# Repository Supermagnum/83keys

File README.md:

# 83keys
A 83 key keyboard, Norwegian QWERTY/DVORAK ISO style.
It's of course possible to use other languages, as the MX cherry switches will accept keycaps with whatever language you need.

It uses 83 1N4148 diodes and three LED's for caps lock,scroll lock, and QWERTY/DVORAK.
It also needs pin headers that accepts the pins from a Teensy++2.0.

That makes it easy to replace the Teensy in the case that something goes wrong.
Since the Teensy++2.0 is mounted in a socket, there is no special training required because there are no need to solder any SMD components. 
I think that that makes it easier to mass produce because little training and special tools are required.

The keyboard layout is located here:
http://www.keyboard-layout-editor.com/#/gists/53284f72c23040b29def237b7399e567

Made using Kicad, that can be found here:
https://kicad-pcb.org/

All footprints for the components needed for the keyboard is included in this GitHub.
That excludes the Teensy++2.0 board and the components needed for it.

Kicad footprints for Teensy 
https://github.com/XenGi/teensy.pretty

Kicad schematic symbols of Teensy modules:
https://github.com/XenGi/teensy_library

QMK is here:
https://qmk.fm/

The handwire folder contains files necessary to make the bottom,top and switch plates for those who want to handwire the keyboard without using a PCB.
It should be compatible with Cherry Stabilizers. 

I hope that the Teensy socket is wired up correctly.
If not,please fork this repository and make the required changes.

Note: The diodes on the schematic diagram is wrong.

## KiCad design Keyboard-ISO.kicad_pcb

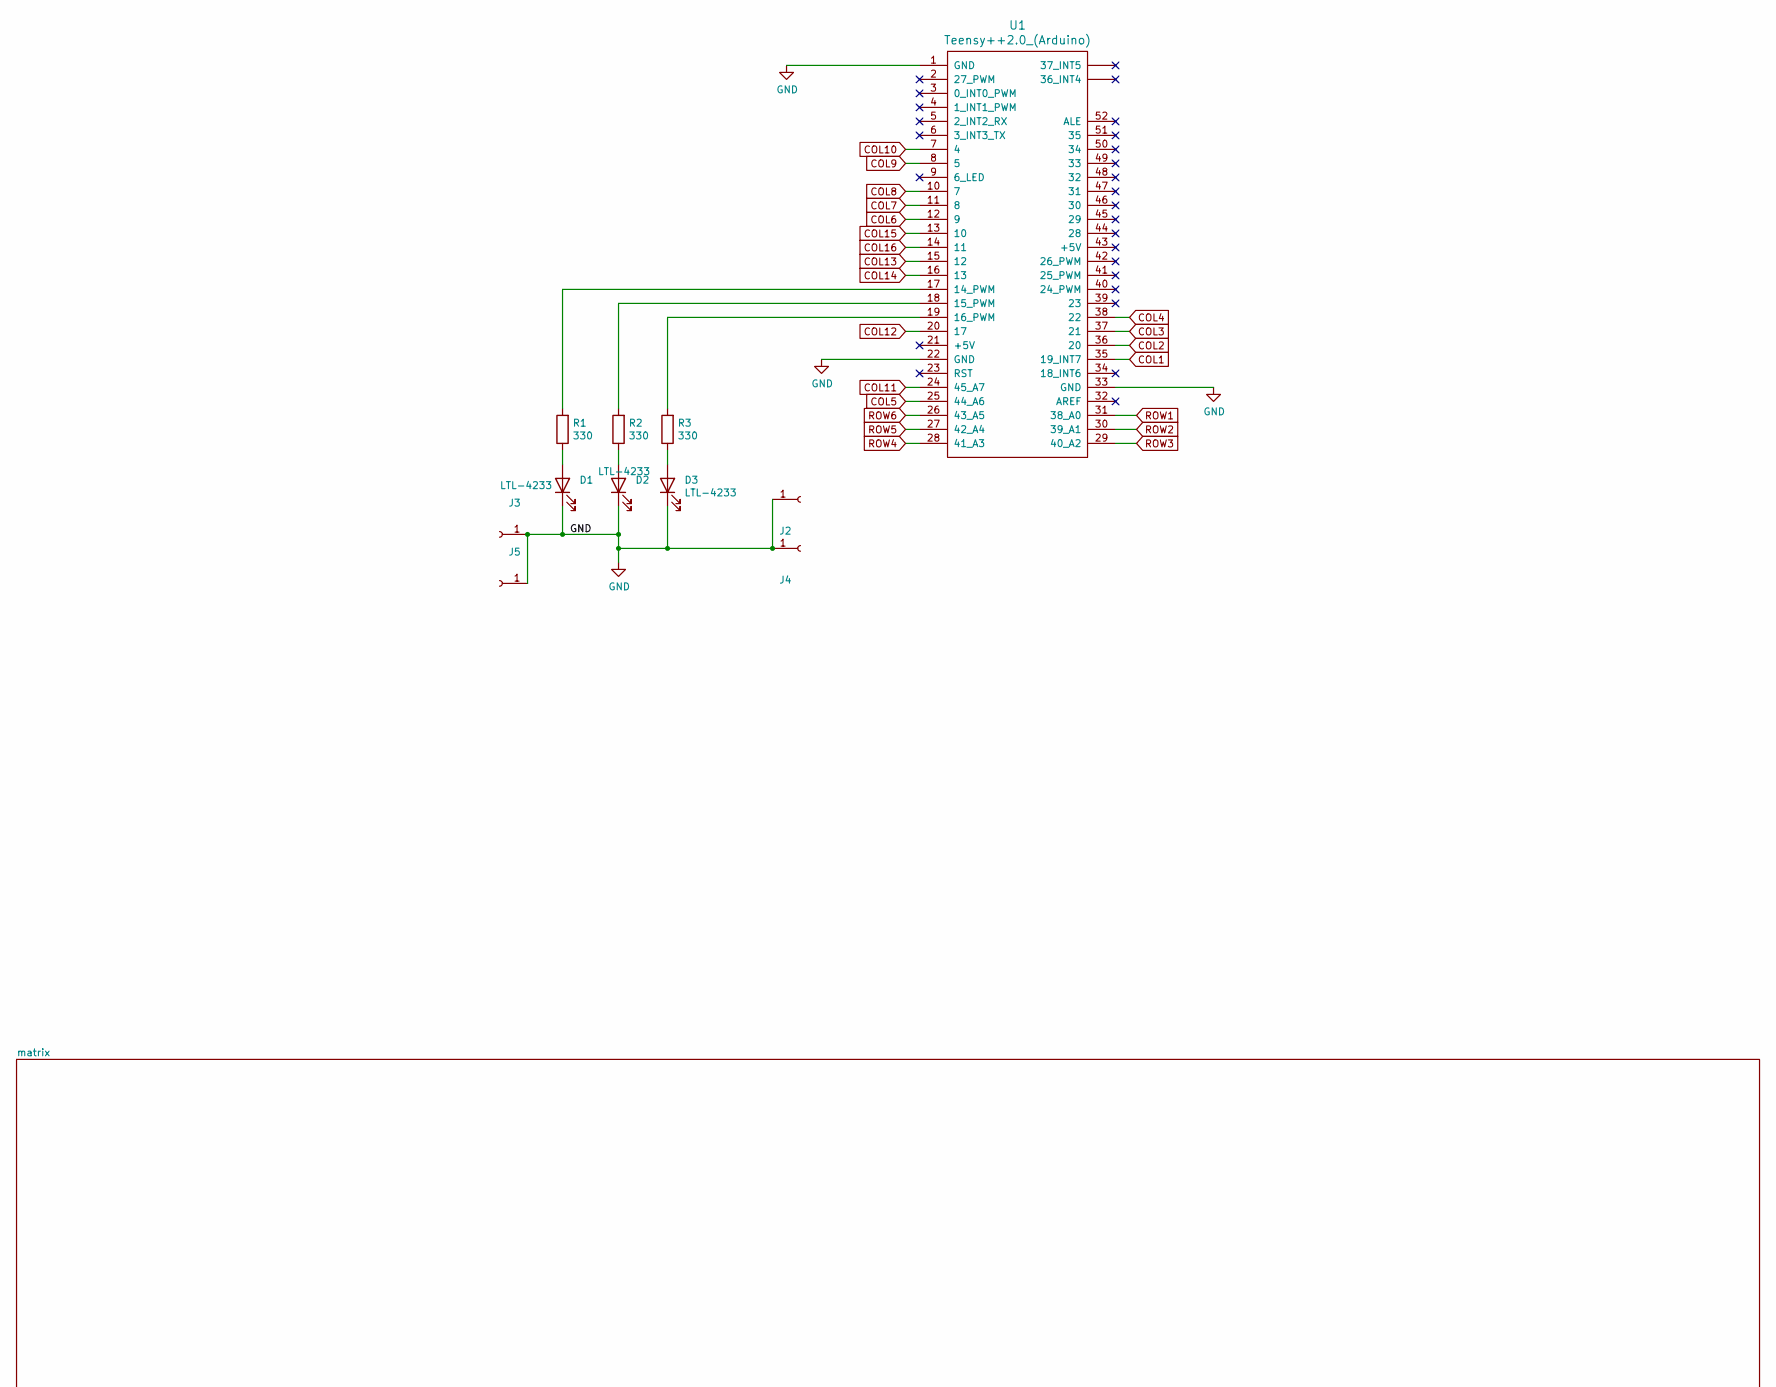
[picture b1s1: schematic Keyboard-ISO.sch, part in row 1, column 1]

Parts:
D1, D2, D3: LTL-4233; D_5KPW_P7.62mm_Vertical_AnodeUp
J2, J3, J4, J5: Conn_01x01_Female; MountingHole_4.5mm_Pad
R1, R2, R3: 330; R_Axial_DIN0204_L3.6mm_D1.6mm_P5.08mm_Horizontal
U1: Teensy++2.0_(Arduino); Teensy2.0-pins-headers

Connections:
COL1: U1.35 (19_INT7); also elsewhere on the board
COL2: U1.36 (20); also elsewhere on the board
COL3: U1.37 (21); also elsewhere on the board
COL4: U1.38 (22); also elsewhere on the board
COL5: U1.25 (44_A6); also elsewhere on the board
COL6: U1.12 (9); also elsewhere on the board
COL7: U1.11 (8); also elsewhere on the board
COL8: U1.10 (7); also elsewhere on the board
COL9: U1.8 (5); also elsewhere on the board
COL10: U1.7 (4); also elsewhere on the board
COL11: U1.24 (45_A7); also elsewhere on the board
COL12: U1.20 (17); also elsewhere on the board
COL13: U1.15 (12); also elsewhere on the board
COL14: U1.16 (13); also elsewhere on the board
COL15: U1.13 (10); also elsewhere on the board
COL16: U1.14 (11); also elsewhere on the board
GND: D1.1 (K), D2.1 (K), D3.1 (K), J2.1, J3.1, J4.1, J5.1, U1.1 (GND), U1.22 (GND), U1.33 (GND)
unnamed: D1.2 (A), R1.1
unnamed: D2.2 (A), R2.1
unnamed: D3.2 (A), R3.1
unnamed: R1.2, U1.17 (14_PWM)
unnamed: R2.2, U1.18 (15_PWM)
unnamed: R3.2, U1.19 (16_PWM)
ROW1: U1.31 (38_A0); also elsewhere on the board
ROW2: U1.30 (39_A1); also elsewhere on the board
ROW3: U1.29 (40_A2); also elsewhere on the board
ROW4: U1.28 (41_A3); also elsewhere on the board
ROW5: U1.27 (42_A4); also elsewhere on the board
ROW6: U1.26 (43_A5); also elsewhere on the board

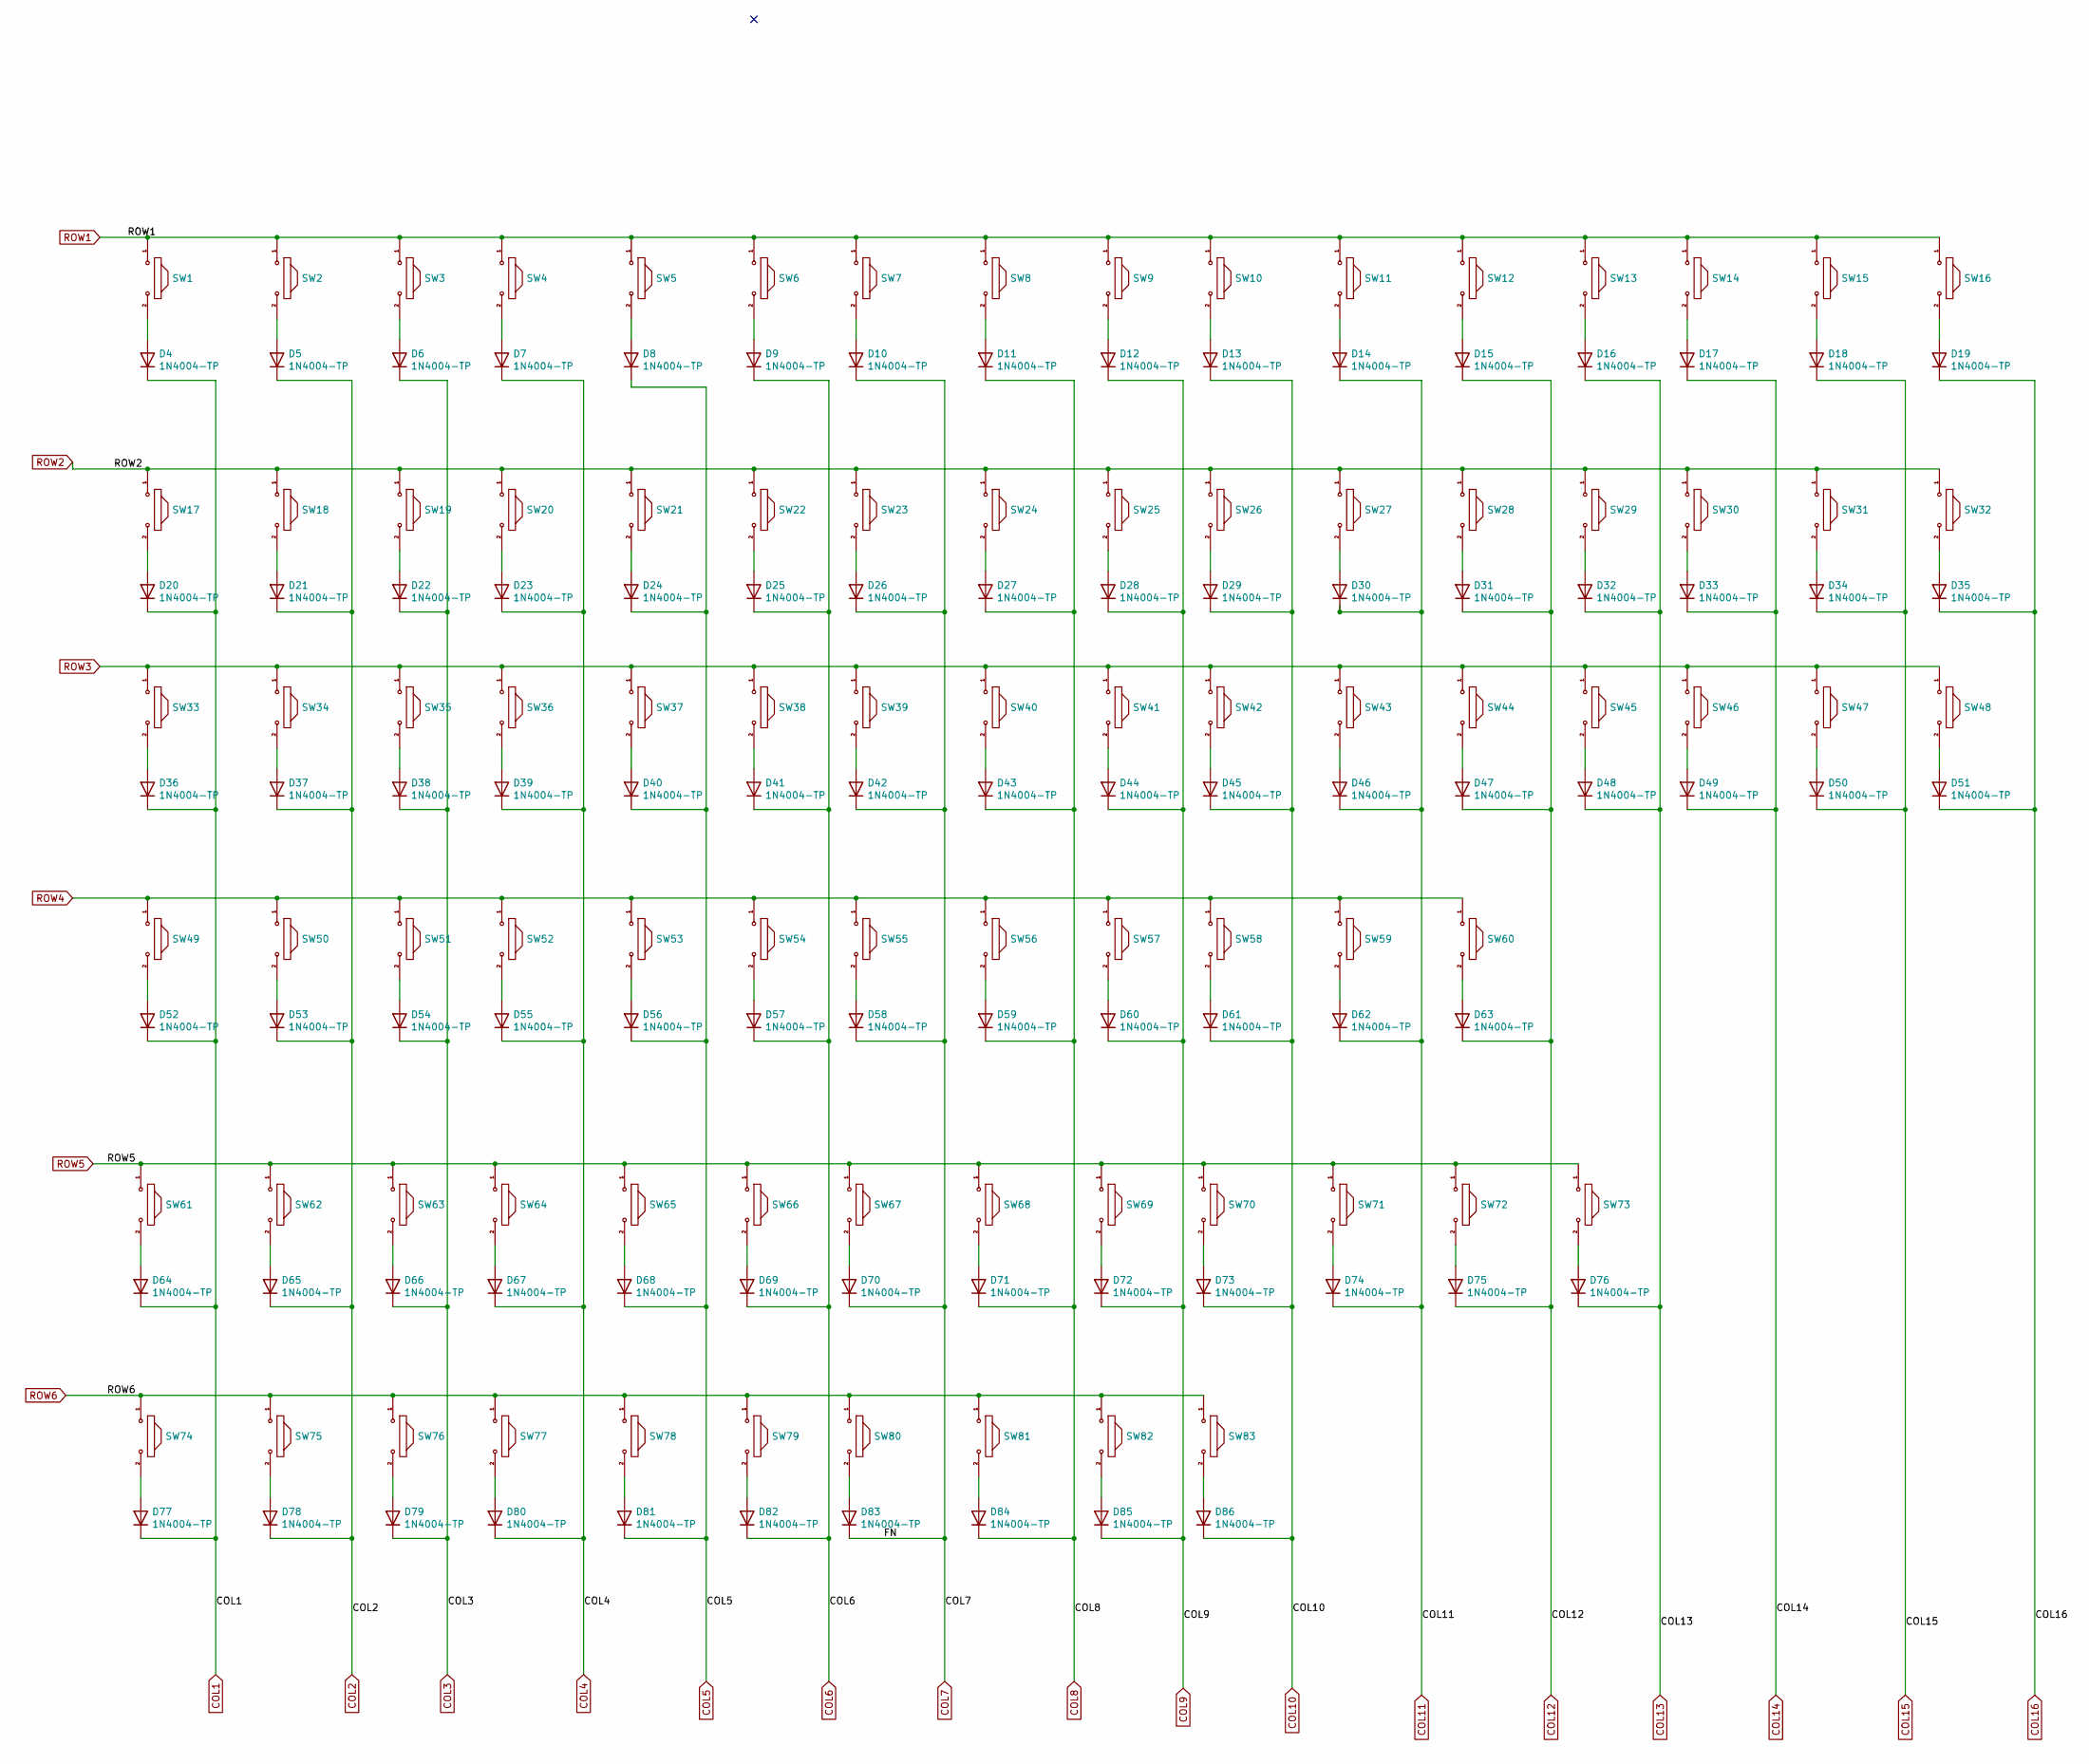
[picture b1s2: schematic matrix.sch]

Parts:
D4, D5, D6, D7, D8, D9, D10, D11, D12, D13, D14, D15, D16, D17, D18, D19, D20, D21, D22, D23, D24, D25, D26, D27, D28, D29, D30, D31, D32, D33, D34, D35, D36, D37, D38, D39, D40, D41, D42, D43, D44, D45, D46, D47, D48, D49, D50, D51, D52, D53, D54, D55, D56, D57, D58, D59, D60, D61, D62, D63, D64, D65, D66, D67, D68, D69, D70, D71, D72, D73, D74, D75, D76, D77, D78, D79, D80, D81, D82, D83, D84, D85, D86: 1N4004-TP; D_A-405_P7.62mm_Horizontal
SW1, SW2, SW3, SW4, SW5, SW6, SW7, SW8, SW9, SW10, SW11, SW12, SW13, SW14, SW15, SW16, SW19, SW20, SW21, SW22, SW23, SW24, SW25, SW26, SW27, SW28, SW31, SW32, SW35, SW36, SW37, SW38, SW39, SW40, SW41, SW42, SW43, SW44, SW46, SW47, SW48, SW49, SW50, SW51, SW52, SW53, SW54, SW55, SW56, SW57, SW58, SW59, SW60, SW61, SW62, SW63, SW64, SW65, SW66, SW67, SW68, SW69, SW70, SW71, SW76, SW79, SW82, SW83: MX; SW_Cherry_MX_1.00u_PCB-NO-LED
SW17, SW29, SW33, SW74, SW80: SW_Cherry_MX_1.50u_PCB
SW18, SW30, SW34, SW73, SW75, SW78, SW81: MX; SW_Cherry_MX_1.00u_PCB
SW45: MX; SW_Cherry_MX_ISOEnter_PCB
SW72: MX; SW_Cherry_MX_1.75u_PCB
SW77: SW_Cherry_MX_6.26u_PCB; SW_Cherry_MX_6.25u_PCB

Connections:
COL1: D4.1 (K), D20.1 (K), D36.1 (K), D52.1 (K), D64.1 (K), D77.1 (K); also elsewhere on the board
COL2: D5.1 (K), D21.1 (K), D37.1 (K), D53.1 (K), D65.1 (K), D78.1 (K); also elsewhere on the board
COL3: D6.1 (K), D22.1 (K), D38.1 (K), D54.1 (K), D66.1 (K), D79.1 (K); also elsewhere on the board
COL4: D7.1 (K), D23.1 (K), D39.1 (K), D55.1 (K), D67.1 (K), D80.1 (K); also elsewhere on the board
COL5: D8.1 (K), D24.1 (K), D40.1 (K), D56.1 (K), D68.1 (K), D81.1 (K); also elsewhere on the board
COL6: D9.1 (K), D25.1 (K), D41.1 (K), D57.1 (K), D69.1 (K), D82.1 (K); also elsewhere on the board
COL7: D10.1 (K), D26.1 (K), D42.1 (K), D58.1 (K), D70.1 (K), D83.1 (K); also elsewhere on the board
COL8: D11.1 (K), D27.1 (K), D43.1 (K), D59.1 (K), D71.1 (K), D84.1 (K); also elsewhere on the board
COL9: D12.1 (K), D28.1 (K), D44.1 (K), D60.1 (K), D72.1 (K), D85.1 (K); also elsewhere on the board
COL10: D13.1 (K), D29.1 (K), D45.1 (K), D61.1 (K), D73.1 (K), D86.1 (K); also elsewhere on the board
COL11: D14.1 (K), D30.1 (K), D46.1 (K), D62.1 (K), D74.1 (K); also elsewhere on the board
COL12: D15.1 (K), D31.1 (K), D47.1 (K), D63.1 (K), D75.1 (K); also elsewhere on the board
COL13: D16.1 (K), D32.1 (K), D48.1 (K), D76.1 (K); also elsewhere on the board
COL14: D17.1 (K), D33.1 (K), D49.1 (K); also elsewhere on the board
COL15: D18.1 (K), D34.1 (K), D50.1 (K); also elsewhere on the board
COL16: D19.1 (K), D35.1 (K), D51.1 (K); also elsewhere on the board
unnamed: D4.2 (A), SW1.2
unnamed: D5.2 (A), SW2.2
unnamed: D6.2 (A), SW3.2
unnamed: D7.2 (A), SW4.2
unnamed: D8.2 (A), SW5.2
unnamed: D9.2 (A), SW6.2
unnamed: D10.2 (A), SW7.2
unnamed: D11.2 (A), SW8.2
unnamed: D12.2 (A), SW9.2
unnamed: D13.2 (A), SW10.2
unnamed: D14.2 (A), SW11.2
unnamed: D15.2 (A), SW12.2
unnamed: D16.2 (A), SW13.2
unnamed: D17.2 (A), SW14.2
unnamed: D18.2 (A), SW15.2
unnamed: D19.2 (A), SW16.2
unnamed: D20.2 (A), SW17.2
unnamed: D21.2 (A), SW18.2
unnamed: D22.2 (A), SW19.2
unnamed: D23.2 (A), SW20.2
unnamed: D24.2 (A), SW21.2
unnamed: D25.2 (A), SW22.2
unnamed: D26.2 (A), SW23.2
unnamed: D27.2 (A), SW24.2
unnamed: D28.2 (A), SW25.2
unnamed: D29.2 (A), SW26.2
unnamed: D30.2 (A), SW27.2
unnamed: D31.2 (A), SW28.2
unnamed: D32.2 (A), SW29.2
unnamed: D33.2 (A), SW30.2
unnamed: D34.2 (A), SW31.2
unnamed: D35.2 (A), SW32.2
unnamed: D36.2 (A), SW33.2
unnamed: D37.2 (A), SW34.2
unnamed: D38.2 (A), SW35.2
unnamed: D39.2 (A), SW36.2
unnamed: D40.2 (A), SW37.2
unnamed: D41.2 (A), SW38.2
unnamed: D42.2 (A), SW39.2
unnamed: D43.2 (A), SW40.2
unnamed: D44.2 (A), SW41.2
unnamed: D45.2 (A), SW42.2
unnamed: D46.2 (A), SW43.2
unnamed: D47.2 (A), SW44.2
unnamed: D48.2 (A), SW45.2
unnamed: D49.2 (A), SW46.2
unnamed: D50.2 (A), SW47.2
unnamed: D51.2 (A), SW48.2
unnamed: D52.2 (A), SW49.2
unnamed: D53.2 (A), SW50.2
unnamed: D54.2 (A), SW51.2
unnamed: D55.2 (A), SW52.2
unnamed: D56.2 (A), SW53.2
unnamed: D57.2 (A), SW54.2
unnamed: D58.2 (A), SW55.2
unnamed: D59.2 (A), SW56.2
unnamed: D60.2 (A), SW57.2
unnamed: D61.2 (A), SW58.2
unnamed: D62.2 (A), SW59.2
unnamed: D63.2 (A), SW60.2
unnamed: D64.2 (A), SW61.2
unnamed: D65.2 (A), SW62.2
unnamed: D66.2 (A), SW63.2
unnamed: D67.2 (A), SW64.2
unnamed: D68.2 (A), SW65.2
unnamed: D69.2 (A), SW66.2
unnamed: D70.2 (A), SW67.2
unnamed: D71.2 (A), SW68.2
unnamed: D72.2 (A), SW69.2
unnamed: D73.2 (A), SW70.2
unnamed: D74.2 (A), SW71.2
unnamed: D75.2 (A), SW72.2
unnamed: D76.2 (A), SW73.2
unnamed: D77.2 (A), SW74.2
unnamed: D78.2 (A), SW75.2
unnamed: D79.2 (A), SW76.2
unnamed: D80.2 (A), SW77.2
unnamed: D81.2 (A), SW78.2
unnamed: D82.2 (A), SW79.2
unnamed: D83.2 (A), SW80.2
unnamed: D84.2 (A), SW81.2
unnamed: D85.2 (A), SW82.2
unnamed: D86.2 (A), SW83.2
ROW1: SW1.1, SW2.1, SW3.1, SW4.1, SW5.1, SW6.1, SW7.1, SW8.1, SW9.1, SW10.1, SW11.1, SW12.1, SW13.1, SW14.1, SW15.1, SW16.1; also elsewhere on the board
ROW2: SW17.1, SW18.1, SW19.1, SW20.1, SW21.1, SW22.1, SW23.1, SW24.1, SW25.1, SW26.1, SW27.1, SW28.1, SW29.1, SW30.1, SW31.1, SW32.1; also elsewhere on the board
ROW3: SW33.1, SW34.1, SW35.1, SW36.1, SW37.1, SW38.1, SW39.1, SW40.1, SW41.1, SW42.1, SW43.1, SW44.1, SW45.1, SW46.1, SW47.1, SW48.1; also elsewhere on the board
ROW4: SW49.1, SW50.1, SW51.1, SW52.1, SW53.1, SW54.1, SW55.1, SW56.1, SW57.1, SW58.1, SW59.1, SW60.1; also elsewhere on the board
ROW5: SW61.1, SW62.1, SW63.1, SW64.1, SW65.1, SW66.1, SW67.1, SW68.1, SW69.1, SW70.1, SW71.1, SW72.1, SW73.1; also elsewhere on the board
ROW6: SW74.1, SW75.1, SW76.1, SW77.1, SW78.1, SW79.1, SW80.1, SW81.1, SW82.1, SW83.1; also elsewhere on the board

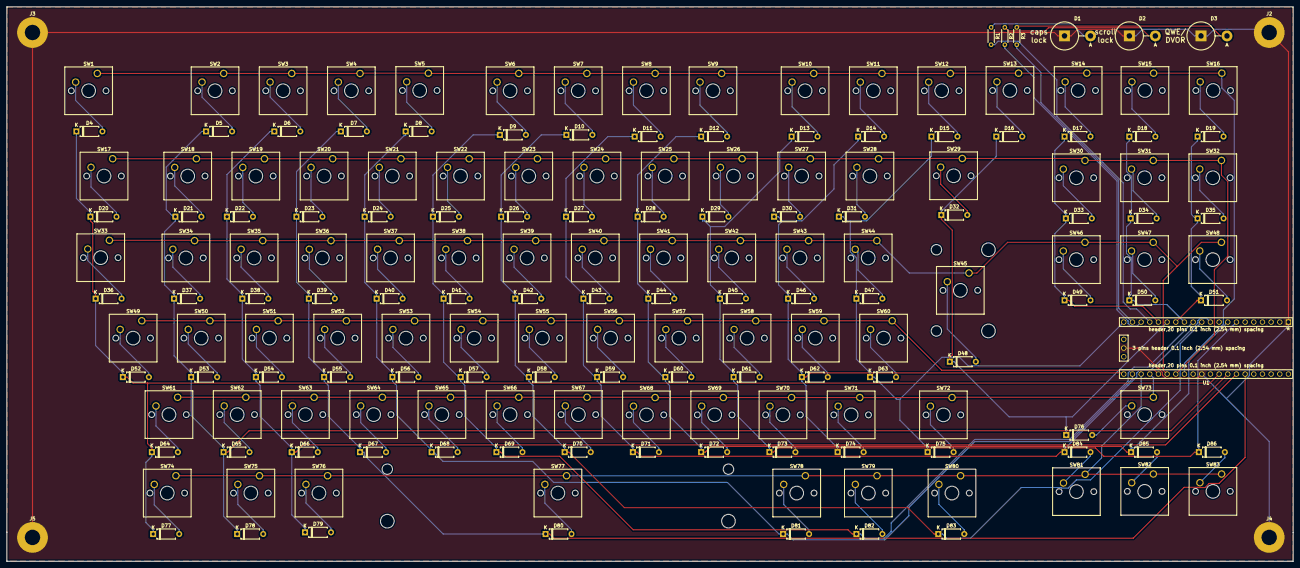
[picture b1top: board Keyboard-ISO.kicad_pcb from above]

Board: 2 copper layers, 377.0 x 162.5 mm, 177 parts (0 on the bottom side), 112 nets.

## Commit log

2020-07-23 added more files,and footprint library
2020-07-23 added electric schema
2020-07-24 Update README.md
    Spell check.
2020-07-24 Add files via upload
    Added files necessary for laser cutting and wiring by hand, without a PCB.
2020-07-24 Add files via upload
    Added pdf drawings, switch mount,top and bottom.
2020-07-24 Update README.md
    Added description.
2020-07-24 Add files via upload
    updated files, and added pictures of PCB and key layouts
2020-07-24 Add files via upload
    updated files
2020-07-24 Add files via upload
    updated files.
2020-07-24 updated readme.
2020-07-25 updated files
    Updated files, changed to using a Teensy++2.0 that plugs right in to the board
2020-07-25 Rename Keyboard-ISO.html to Keyboard-ISO-BOM.html
2020-07-26 Update README.md
    Changed to faster diodes.
2020-07-26 Update Keyboard-ISO-BOM.html
    Changed to faster diodes.
2020-07-26 Update README.md
    Updated readme.
2020-07-27 updated gerber files.
    Moved the Teensy++2.0 headers to the backside of the board.
2020-07-30 Add files via upload
    updated gerber files, removed unwanted empty zones.
